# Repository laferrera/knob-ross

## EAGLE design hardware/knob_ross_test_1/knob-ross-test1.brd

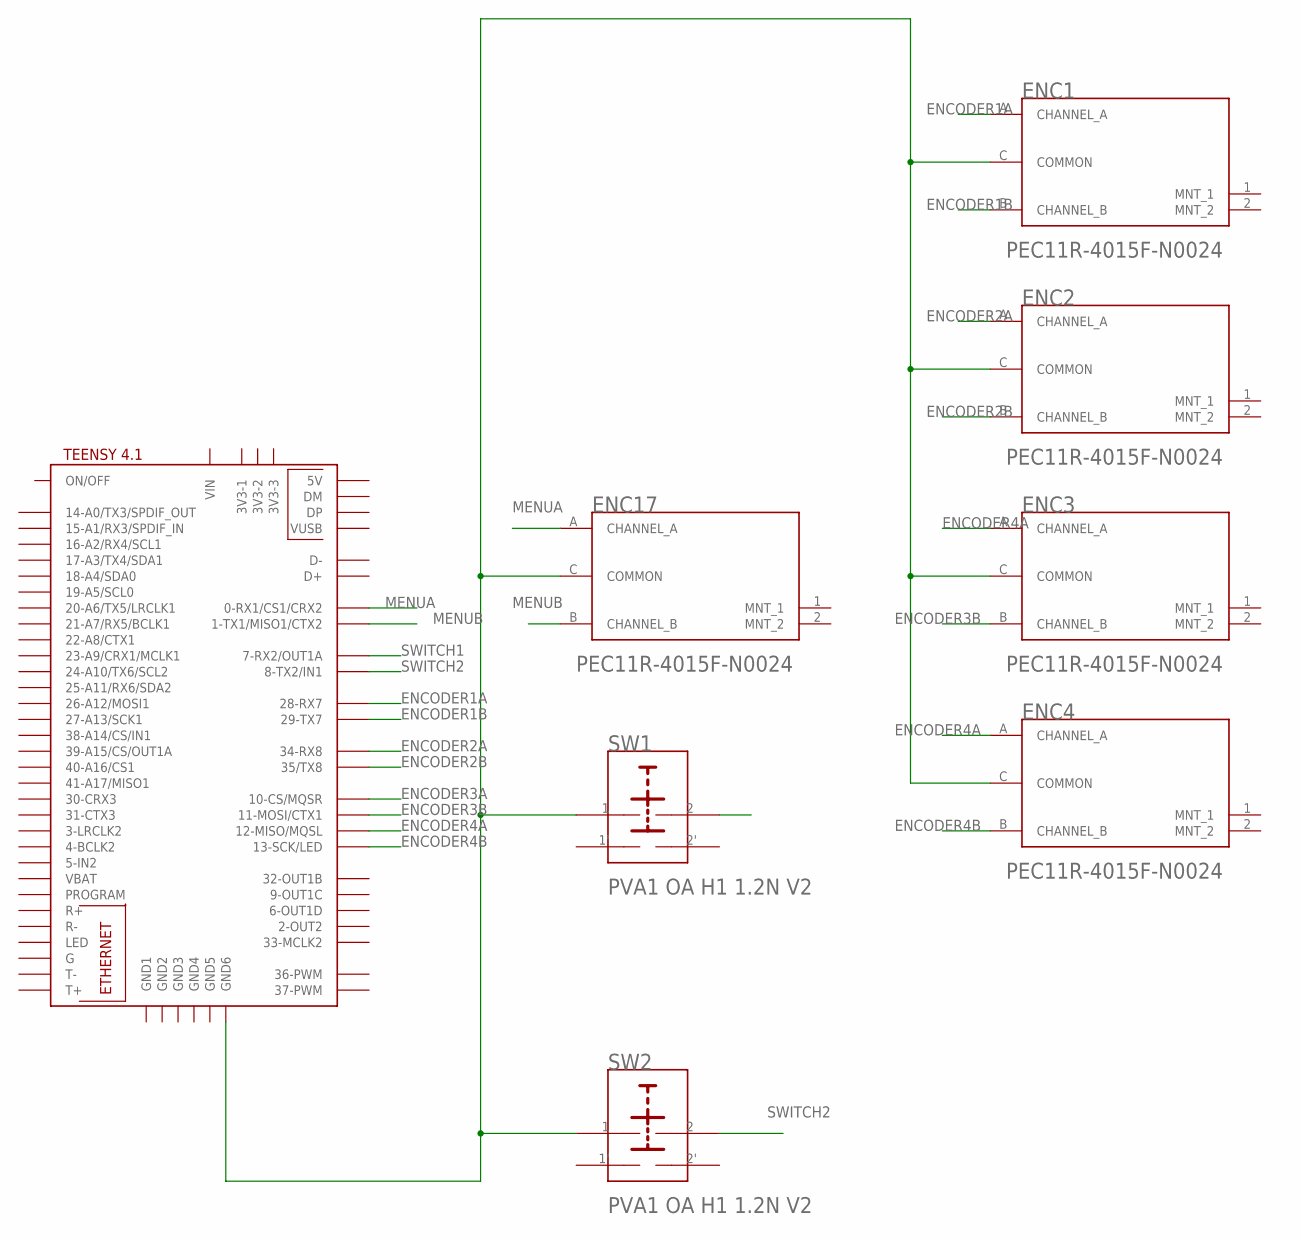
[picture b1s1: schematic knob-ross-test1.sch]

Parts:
ENC1, ENC2, ENC3, ENC4, ENC17: BOURNS_PEC11R-4015F-N0024BOURNS_PEC11R-4015F-N002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; BOURNS_PEC11R-4015F-N0024_0
SW1, SW2: C&K_COMPONENTS_PVA1_OA_H1_1_2N_V2C&K_COMPONENTS_P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; C&K_COMPONENTS_PVA1_OA_H1_1_2N_V2_0
U$1: TEENSY41

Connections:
ENCODER1A: ENC1.A (CHANNEL_A), U$1.28-RX7
ENCODER1B: ENC1.B (CHANNEL_B), U$1.29-TX7
ENCODER2A: ENC2.A (CHANNEL_A), U$1.34-RX8
ENCODER2B: ENC2.B (CHANNEL_B), U$1.35-TX8 (35/TX8)
ENCODER3A: U$1.10-CS\MQSR (10-CS/MQSR)
ENCODER3B: ENC3.B (CHANNEL_B), U$1.11-MOSI/CTX1
ENCODER4A: ENC3.A (CHANNEL_A), ENC4.A (CHANNEL_A), U$1.12-MISO/MQSL
ENCODER4B: ENC4.B (CHANNEL_B), U$1.13-SCK/LED
MENUA: ENC17.A (CHANNEL_A), U$1.0-RX1/CS1/CRX2
MENUB: ENC17.B (CHANNEL_B), U$1.1-TX1/MISO1/CTX2
unnamed: ENC1.C (COMMON), ENC2.C (COMMON), ENC3.C (COMMON), ENC4.C (COMMON), ENC17.C (COMMON), SW1.1, SW2.1, U$1.GND6
SWITCH1: SW1.2, U$1.7-RX2/OUT1A
SWITCH2: SW2.2, U$1.8-TX2/IN1

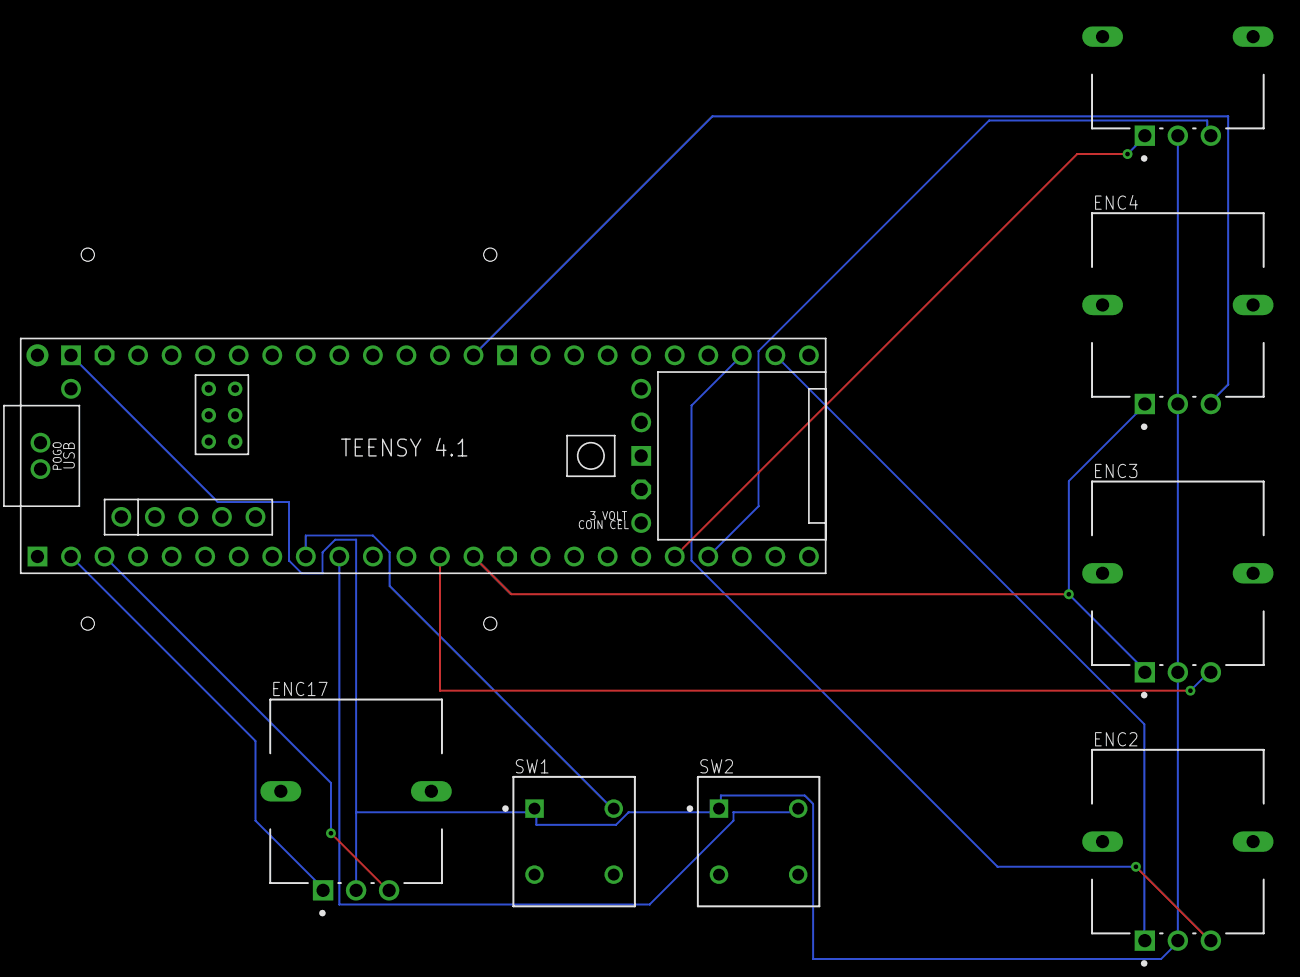
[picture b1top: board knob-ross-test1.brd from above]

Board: 2 copper layers, 8 parts (0 on the bottom side), 12 nets.

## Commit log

2022-03-01 mostly working
2022-03-02 starting render loops
2022-03-03 refactoring
2022-03-03 about to make big changes
2022-03-03 almost there
2022-03-04 done for the day
2022-03-04 in a semi-functional state, asking nate for help.
2022-03-04 slightly better
2022-03-05 getting better all the time
2022-03-06 checking in the GEM library that i am destroying
2022-03-06 about to do some serious damage
2022-03-06 lfos starting to work
2022-03-07 about to rename knobs to channels
2022-03-08 starting accumulator
2022-03-08 accum working?
2022-03-08 about to make some weird decisions
2022-03-08 trying to figure out lfos
2022-03-09 this is hard
2022-03-09 more work!
2022-03-09 fixing stuffs
2022-03-09 in a good place
2022-03-09 starting graphs
2022-03-09 graphs are mostly working
2022-03-09 no crashes after 5 minutes
2022-03-09 more cleanup
2022-03-09 you can set freq now
2022-03-10 adding clipping
2022-03-11 more stuff
2022-03-11 renaming the project
2022-03-11 git removing the ds stores
2022-03-11 random working
2022-03-25 starting to build offsets
2022-03-25 adding bios style startupscreen
2022-03-29 tap tempo
2022-03-29 tap tempo workin
2022-03-29 everything in shambles, but working
2022-03-29 global bpm
2022-03-29 little by little
2022-03-29 screensaver back
2022-03-29 more refactoring, almost got hiding working
2022-03-30 doing lots of things
2022-03-30 figuring out hidden menu
2022-03-30 I think i figured it out
2022-03-30 werkin
2022-03-30 a lot of work to fix this menu
2022-03-31 maybe figured out samplerate?
2022-03-31 better timing
